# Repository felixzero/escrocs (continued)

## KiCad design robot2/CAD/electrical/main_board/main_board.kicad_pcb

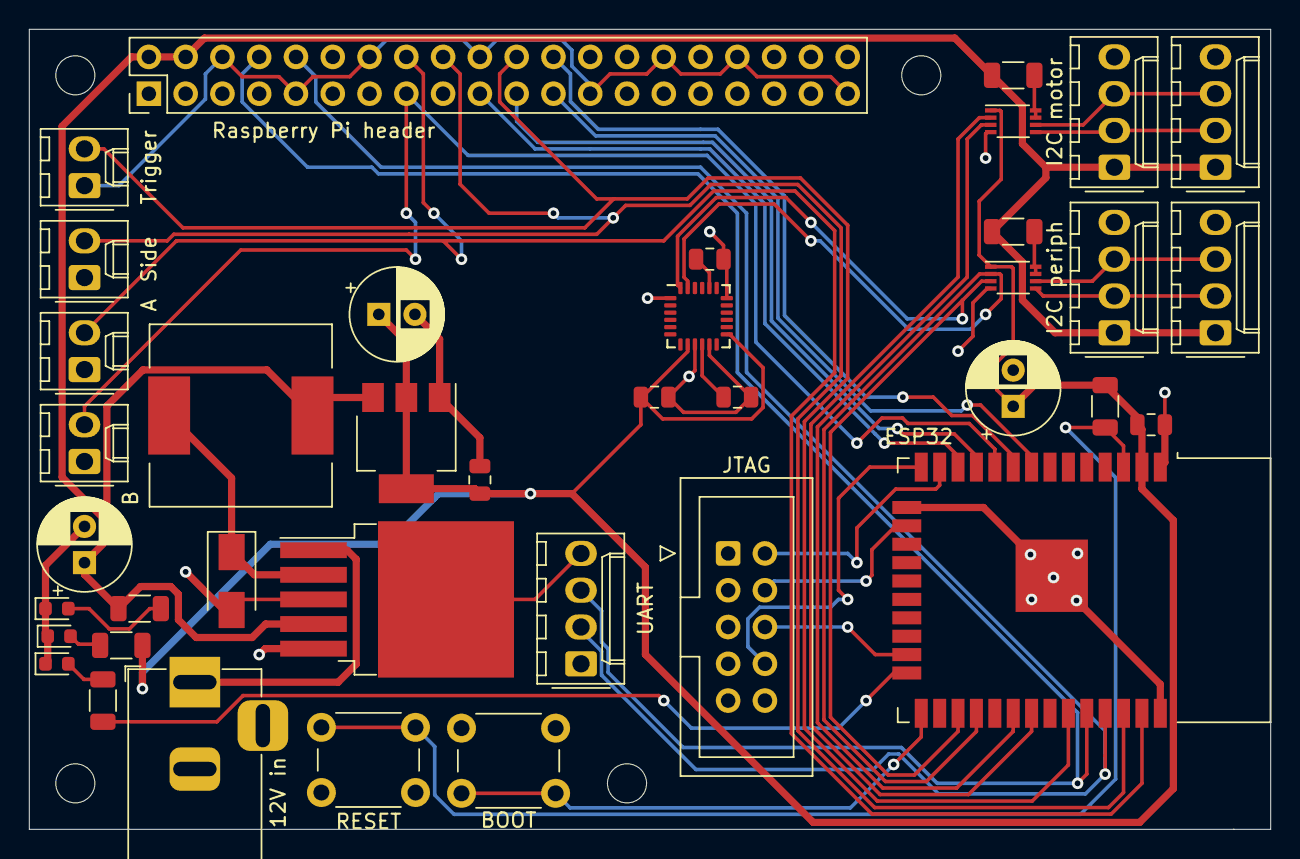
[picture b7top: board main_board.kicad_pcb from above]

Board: 2 copper layers, 85.7 x 55.2 mm, 39 parts (0 on the bottom side), 37 nets.

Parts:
12V in: Battery in; BarrelJack_Horizontal
A: Button A; Molex_KK-254_AE-6410-02A_1x02_P2.54mm_Vertical
B: Button B; Molex_KK-254_AE-6410-02A_1x02_P2.54mm_Vertical
BOOT: BOOT; SW_PUSH_6mm
C1, C2, C5: 10u; CP_Radial_D6.3mm_P2.50mm
C3, C4, C6, C7: 100n; C_0805_2012Metric
C8: 2.2n 50V; C_0805_2012Metric
D1: SS54; D_SMA
D2: 5V power; LED_0603_1608Metric
D3: 3V3 power; LED_0603_1608Metric
D4: Status; LED_0603_1608Metric
ESP32: ESP32-WROOM-32
I2C motor: I2C Motor; Molex_KK-254_AE-6410-04A_1x04_P2.54mm_Vertical
I2C periph: I2C Peripheral; Molex_KK-254_AE-6410-04A_1x04_P2.54mm_Vertical
J7: I2C Peripheral; Molex_KK-254_AE-6410-04A_1x04_P2.54mm_Vertical
J10: I2C Motor; Molex_KK-254_AE-6410-04A_1x04_P2.54mm_Vertical
JTAG: JTAG; IDC-Header_2x05_P2.54mm_Vertical
L1: 100u; L_12x12mm_H6mm
R1: 220; R_1206_3216Metric
R2: 10k; R_1206_3216Metric
R3, R4: 100; R_1206_3216Metric
R5, R6: 200k; R_1206_3216Metric
RESET: RESET; SW_PUSH_6mm
Raspberry Pi header: Raspberry_Pi_2_3_4; PinHeader_2x20_P2.54mm_Vertical
Side: Side select; Molex_KK-254_AE-6410-02A_1x02_P2.54mm_Vertical
Trigger: Trigger; Molex_KK-254_AE-6410-02A_1x02_P2.54mm_Vertical
U1: LM2576S-5; TO-263-5_TabPin3
U2: AMS1117-3.3; SOT-223-3_TabPin2
U4, U5: PCA9306DC; VSSOP-8_2.3x2mm_P0.5mm
U6: MPU-6050; InvenSense_QFN-24_4x4mm_P0.5mm
UART: UART PGM; Molex_KK-254_AE-6410-04A_1x04_P2.54mm_Vertical

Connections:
+3V3: C2.1, C3.1, C4.1, C5.1, C7.1, ESP32.2, R2.1, R3.1, U2.2, U4.1, U5.1, U6.8, U6.13
+5V: C1.1, I2C motor.1, I2C periph.1, J7.1, J10.1, L1.2, R1.1, R5.1, R6.1, Raspberry Pi header.2, Raspberry Pi header.4, U1.4, U2.3
/BTN_A: A.2, ESP32.37, Raspberry Pi header.16
/BTN_B: B.2, ESP32.10, Raspberry Pi header.15
/JTAG_TCK: ESP32.16, JTAG.4
/JTAG_TDI: ESP32.14, JTAG.8
/JTAG_TDO: ESP32.23, JTAG.6
/JTAG_TMS: ESP32.13, JTAG.2
/SCL_MOTOR: ESP32.31, U5.2
/SCL_PERIPH: ESP32.28, U4.2, U6.23
/SDA_MOTOR: ESP32.30, U5.3
/SDA_PERIPH: ESP32.27, U4.3, U6.24
/SIDE_BTN: ESP32.36, Raspberry Pi header.18, Side.2
/SPI_CLK: ESP32.8, Raspberry Pi header.23
/SPI_CS0: ESP32.9, Raspberry Pi header.24
/SPI_MISO: ESP32.11, Raspberry Pi header.21
/SPI_MOSI: ESP32.12, Raspberry Pi header.19
/TRIG_BTN: ESP32.33, Raspberry Pi header.22, Trigger.2
/UART_MISO: ESP32.35, Raspberry Pi header.10, UART.2
/UART_MOSI: ESP32.34, Raspberry Pi header.8, UART.3
GND: 12V in.2, A.1, B.1, BOOT.1, C1.2, C2.2, C3.2, C4.2, C5.2, C6.2, C7.2, C8.2, D1.2, D2.1, D3.1, D4.1, ESP32.1, ESP32.15, ESP32.38, ESP32.39, I2C motor.4, I2C periph.4, J7.4, J10.4, JTAG.3, JTAG.5, JTAG.7, JTAG.9, RESET.1, Raspberry Pi header.6, Raspberry Pi header.9, Raspberry Pi header.14, Raspberry Pi header.20, Raspberry Pi header.25, Raspberry Pi header.30, Raspberry Pi header.34, Raspberry Pi header.39, Side.1, Trigger.1, U1.3, U1.5, U2.1, U4.4, U5.4, U6.1, U6.9, U6.11, U6.18, UART.4
unnamed: C6.1, U6.10
unnamed: C8.1, U6.20
unnamed: D1.1, L1.1, U1.2
unnamed: D2.2, R1.2
unnamed: D3.2, R3.2
unnamed: D4.2, R4.2
unnamed: 12V in.1, U1.1
unnamed: I2C periph.2, J7.2, U4.5
unnamed: I2C periph.3, J7.3, U4.6
unnamed: I2C motor.2, J10.2, U5.5
unnamed: I2C motor.3, J10.3, U5.6
unnamed: ESP32.3, R2.2, RESET.2
unnamed: ESP32.24, R4.1
unnamed: R5.2, U4.7, U4.8
unnamed: R6.2, U5.7, U5.8
unnamed: BOOT.2, ESP32.25

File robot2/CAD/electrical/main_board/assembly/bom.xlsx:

Comment | Designator | Footprint | LCSC part number
100n | C3,C4,C6,C7 | Capacitor_SMD:C_0805_2012Metric | C28233
2.2n 50V | C8 | Capacitor_SMD:C_0805_2012Metric | C28260
SS54 | D1 | Diode_SMD:D_SMA | C22452
Status LED | D2,D3,D4 | LED_SMD:LED_0603_1608Metric | C72038
100u | L1 | Inductor_SMD:L_12x12mm_H6mm | C169378
300 | R1 | Resistor_SMD:R_1206_3216Metric | C17887
10k | R2 | Resistor_SMD:R_1206_3216Metric | C17902
100 | R3,R4 | Resistor_SMD:R_1206_3216Metric | C17901
100k | R5,R6 | Resistor_SMD:R_1206_3216Metric | C17900
LM2576S-5 | U1 | Package_TO_SOT_SMD:TO-263-5_TabPin3 | C34465
AMS1117-3.3 | U2 | Package_TO_SOT_SMD:SOT-223-3_TabPin2 | C6186
ESP32-WROOM-32 | U3 | RF_Module:ESP32-WROOM-32 | C82899
PCA9306DC | U4,U5 | Package_SO:VSSOP-8_2.3x2mm_P0.5mm | C129510
MPU-6050 | U6 | Sensor_Motion:InvenSense_QFN-24_4x4mm_P0.5mm | C24112
